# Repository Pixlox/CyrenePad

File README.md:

# CyrenePad
A simple macropad, created as a Hack Club hackpad. Dedicated to Cyrene from Honkai: Star Rail... for some reason.

> This will be a romantic story like none that has come before... you think so too, right?

## CAD
It's pretty simple. I've added some Cyrene branding to it, though.

## PCB
Here's the PCB! First time doing something like this too!

And, here's the 3D model!

## Firmware
I got (hopefully) the firmware to show this image.

It's made in QMK. The encoder controls volume, and LED brightness. The keys are currently mapped to F13-16!

## BOM
- 4x Cherry MX Switches
- 4x DSA Keycaps
- 4x SK6812 MINI-E LEDs
- 1x 0.91" 128x32 OLED Display
- 1x EC11 Rotary Encoder
- 1x XIAO RP2040
- 1x Case (2 printed parts)

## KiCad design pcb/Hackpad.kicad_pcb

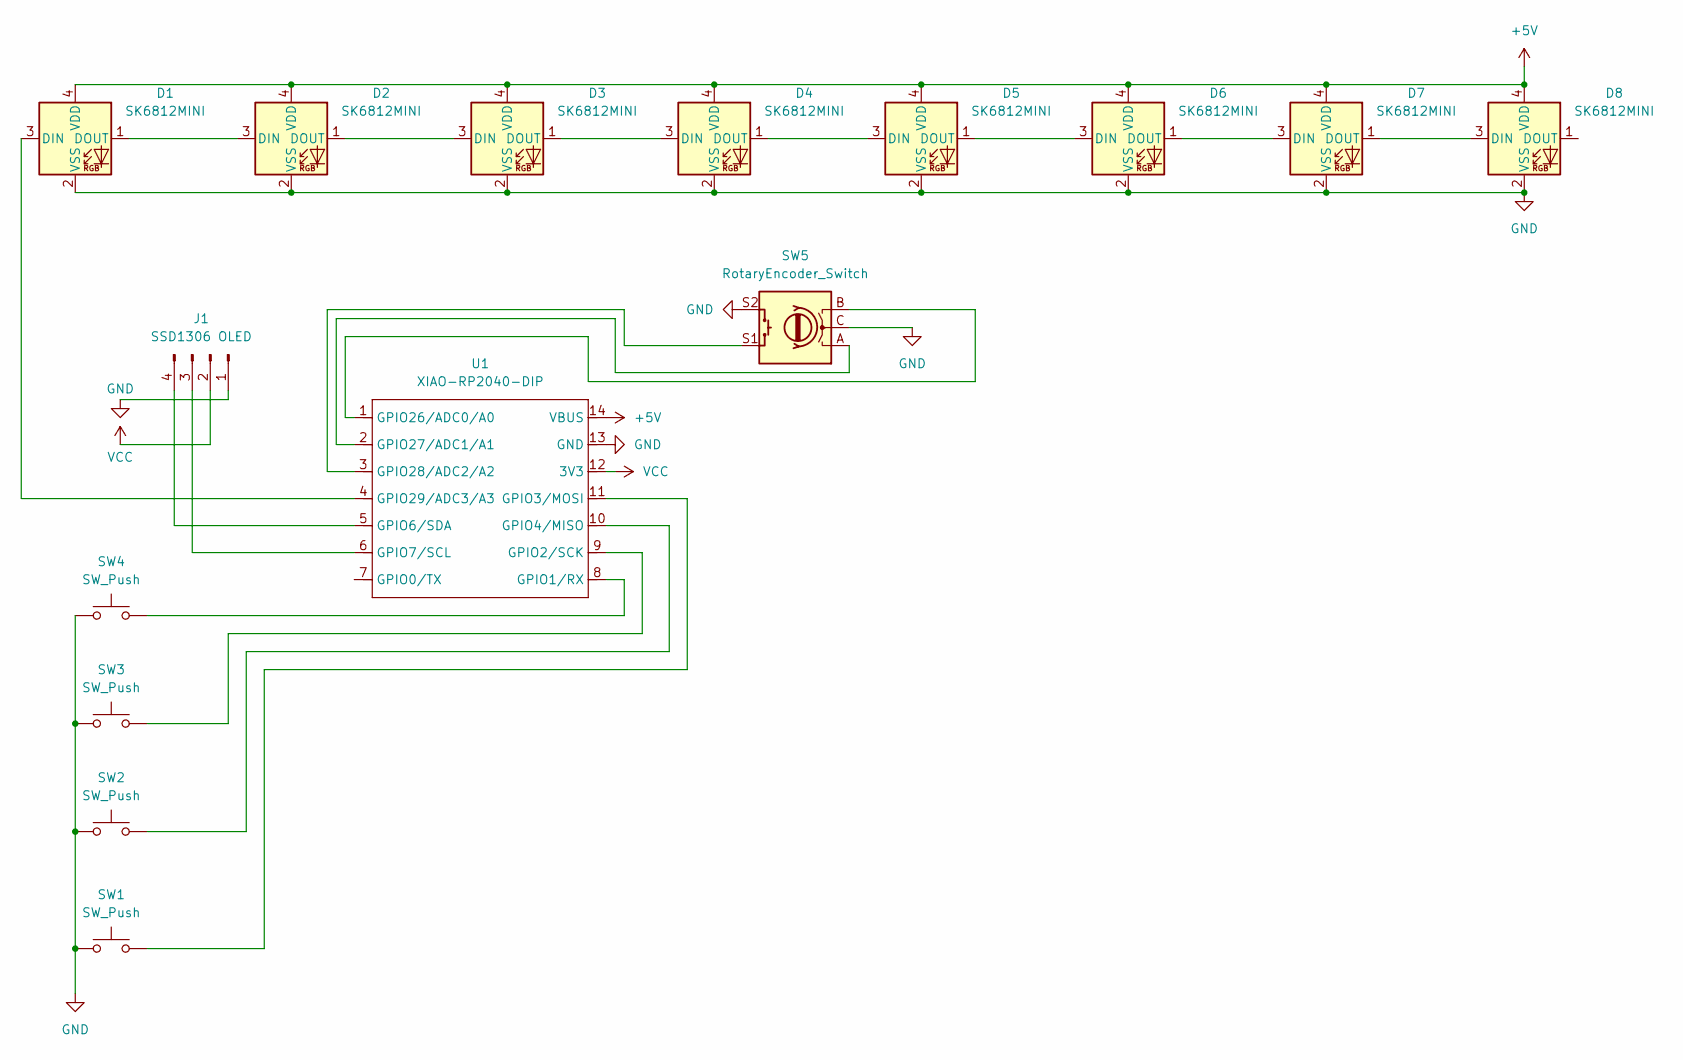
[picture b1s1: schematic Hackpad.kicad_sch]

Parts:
D1, D2, D3, D4, D5, D6, D7, D8: SK6812MINI; LED_MX_6028R
J1: SSD1306 OLED; SSD1306-0.91-OLED-4pin-128x32
SW1, SW2, SW3, SW4: SW_Push; SW_Cherry_MX_1.00u_PCB
SW5: RotaryEncoder_Switch; RotaryEncoder_Alps_EC11E-Switch_Vertical_H20mm
U1: XIAO-RP2040-DIP

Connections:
+5V: D1.4 (VDD), D2.4 (VDD), D3.4 (VDD), D4.4 (VDD), D5.4 (VDD), D6.4 (VDD), D7.4 (VDD), D8.4 (VDD), U1.14 (VBUS)
GND: D1.2 (VSS), D2.2 (VSS), D3.2 (VSS), D4.2 (VSS), D5.2 (VSS), D6.2 (VSS), D7.2 (VSS), D8.2 (VSS), J1.1, SW1.1, SW2.1, SW3.1, SW4.1, SW5.C, SW5.S2, U1.13 (GND)
unnamed: D1.3 (DIN), U1.4 (GPIO29/ADC3/A3)
unnamed: D1.1 (DOUT), D2.3 (DIN)
unnamed: D2.1 (DOUT), D3.3 (DIN)
unnamed: D3.1 (DOUT), D4.3 (DIN)
unnamed: D4.1 (DOUT), D5.3 (DIN)
unnamed: D5.1 (DOUT), D6.3 (DIN)
unnamed: D6.1 (DOUT), D7.3 (DIN)
unnamed: D7.1 (DOUT), D8.3 (DIN)
unnamed: J1.3, U1.6 (GPIO7/SCL)
unnamed: J1.4, U1.5 (GPIO6/SDA)
unnamed: SW4.2, U1.8 (GPIO1/RX)
unnamed: SW3.2, U1.9 (GPIO2/SCK)
unnamed: SW1.2, U1.11 (GPIO3/MOSI)
unnamed: SW2.2, U1.10 (GPIO4/MISO)
unnamed: SW5.B, U1.1 (GPIO26/ADC0/A0)
unnamed: SW5.A, U1.2 (GPIO27/ADC1/A1)
unnamed: SW5.S1, U1.3 (GPIO28/ADC2/A2)
VCC: J1.2, U1.12 (3V3)

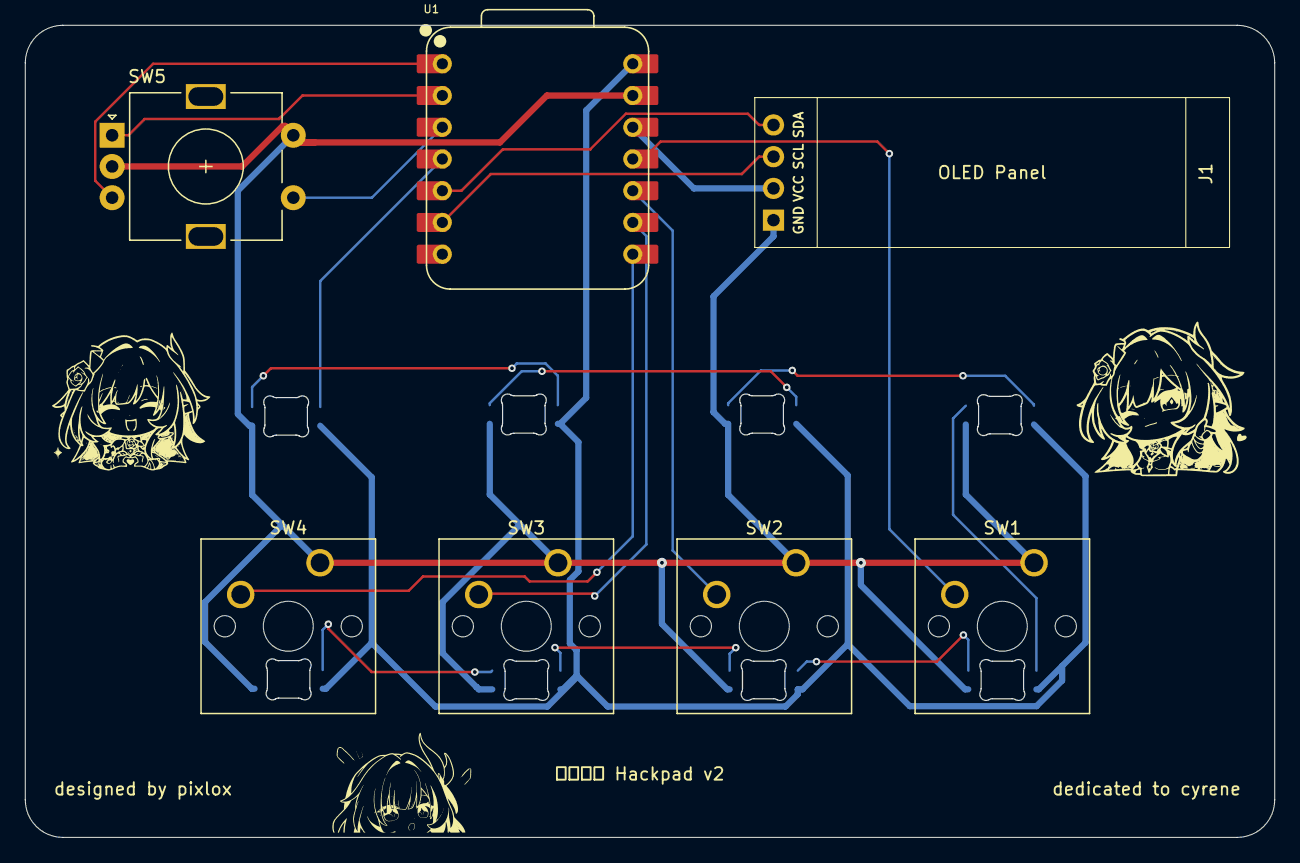
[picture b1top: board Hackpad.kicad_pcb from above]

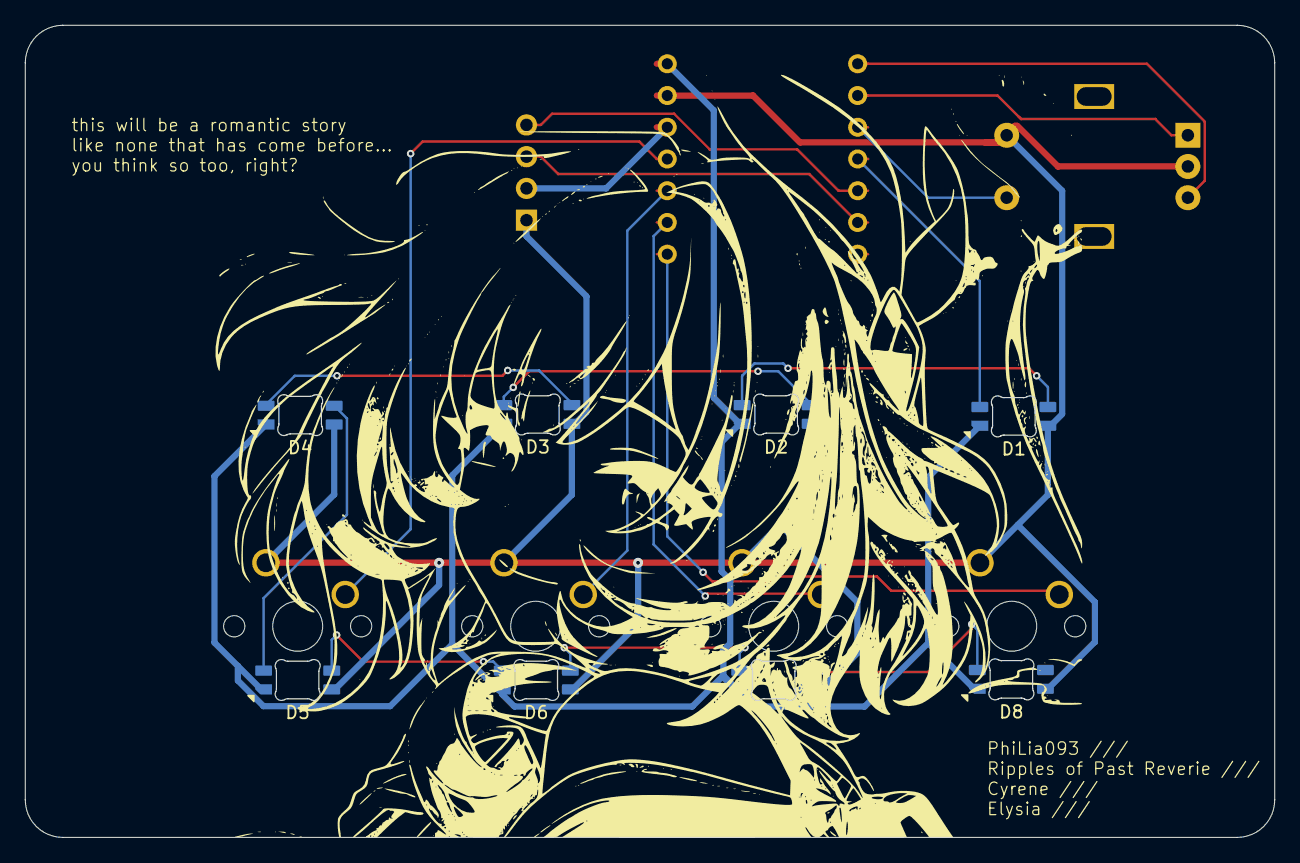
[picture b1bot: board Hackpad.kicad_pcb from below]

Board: 2 copper layers, 100.0 x 65.0 mm, 19 parts (9 on the bottom side), 20 nets.

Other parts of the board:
CyreneBack: LOGO; CyreneSilk
CyreneLeft: LOGO; CyreneChibi1
CyrenePeek: LOGO; CyrenePeeking
CyreneRight: LOGO; CyrenePoint

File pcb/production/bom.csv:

Designator,Footprint,Quantity,Value,LCSC Part #
"D1, D2, D3, D4, D5, D6, D7, D8",LED_MX_6028R,8,SK6812MINI,
J1,SSD1306-0.91-OLED-4pin-128x32,1,SSD1306 OLED,
"SW1, SW2, SW3, SW4",SW_Cherry_MX_1.00u_PCB,4,SW_Push,
SW5,RotaryEncoder_Alps_EC11E-Switch_Vertical_H20mm,1,RotaryEncoder_Switch,
U1,XIAO-RP2040-DIP,1,XIAO-RP2040-DIP,

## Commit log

2026-01-04 gitignore update
2026-01-04 all the files
2026-01-04 readme
2026-01-14 finished!?
2026-02-11 pcb errors. fixed
